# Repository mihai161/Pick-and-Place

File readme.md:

This is my DIY Pick and Place machine powered by OpenPnP

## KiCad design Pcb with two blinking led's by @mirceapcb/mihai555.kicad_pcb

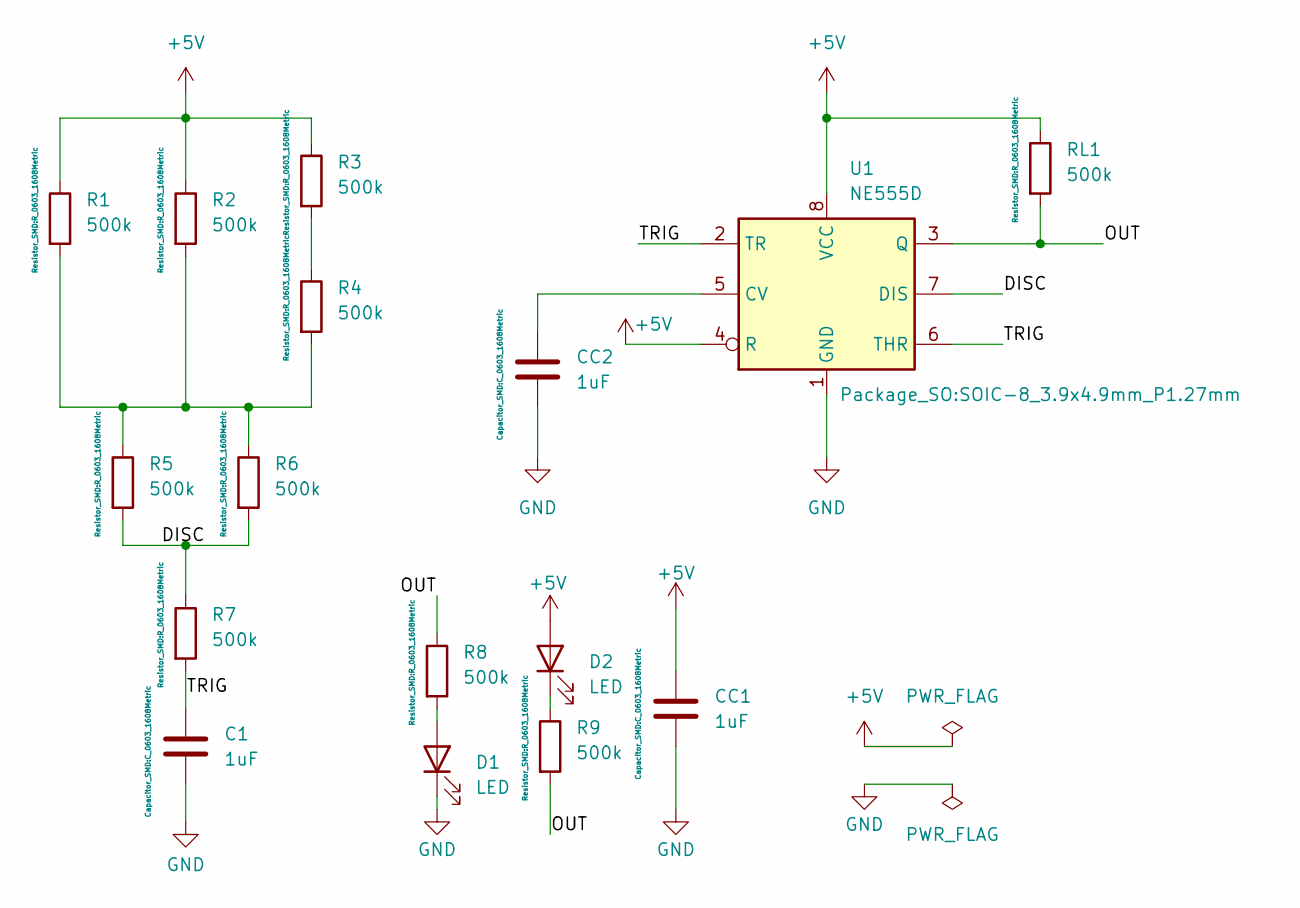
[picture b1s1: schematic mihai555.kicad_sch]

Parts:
C1: 1uF; C_0603_1608Metric
CC1, CC2: 1uF; C_0603_1608Metric
D1, D2: LED; LED_0603_1608Metric
R1, R2, R3, R4, R5, R6, R7, R8, R9: 500k; R_0603_1608Metric
RL1: 500k; R_0603_1608Metric
U1: NE555D; SOIC-8_3.9x4.9mm_P1.27mm

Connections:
+5V: CC1.1, D2.2 (A), R1.1, R2.1, R3.1, RL1.1, U1.4 (R), U1.8 (VCC)
/DISC: R5.2, R6.2, R7.1, U1.7 (DIS)
/OUT: R8.1, R9.2, RL1.2, U1.3 (Q)
/TRIG: C1.1, R7.2, U1.2 (TR), U1.6 (THR)
GND: C1.2, CC1.2, CC2.2, D1.1 (K), U1.1 (GND)
unnamed: D1.2 (A), R8.2
unnamed: D2.1 (K), R9.1
unnamed: R1.2, R2.2, R4.2, R5.1, R6.1
unnamed: R3.2, R4.1
unnamed: CC2.1, U1.5 (CV)

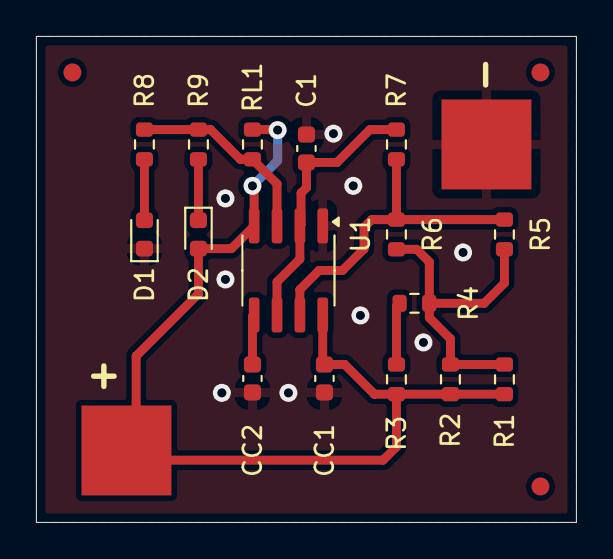
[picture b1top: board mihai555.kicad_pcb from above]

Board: 2 copper layers, 30.0 x 27.0 mm, 16 parts (0 on the bottom side), 10 nets.
